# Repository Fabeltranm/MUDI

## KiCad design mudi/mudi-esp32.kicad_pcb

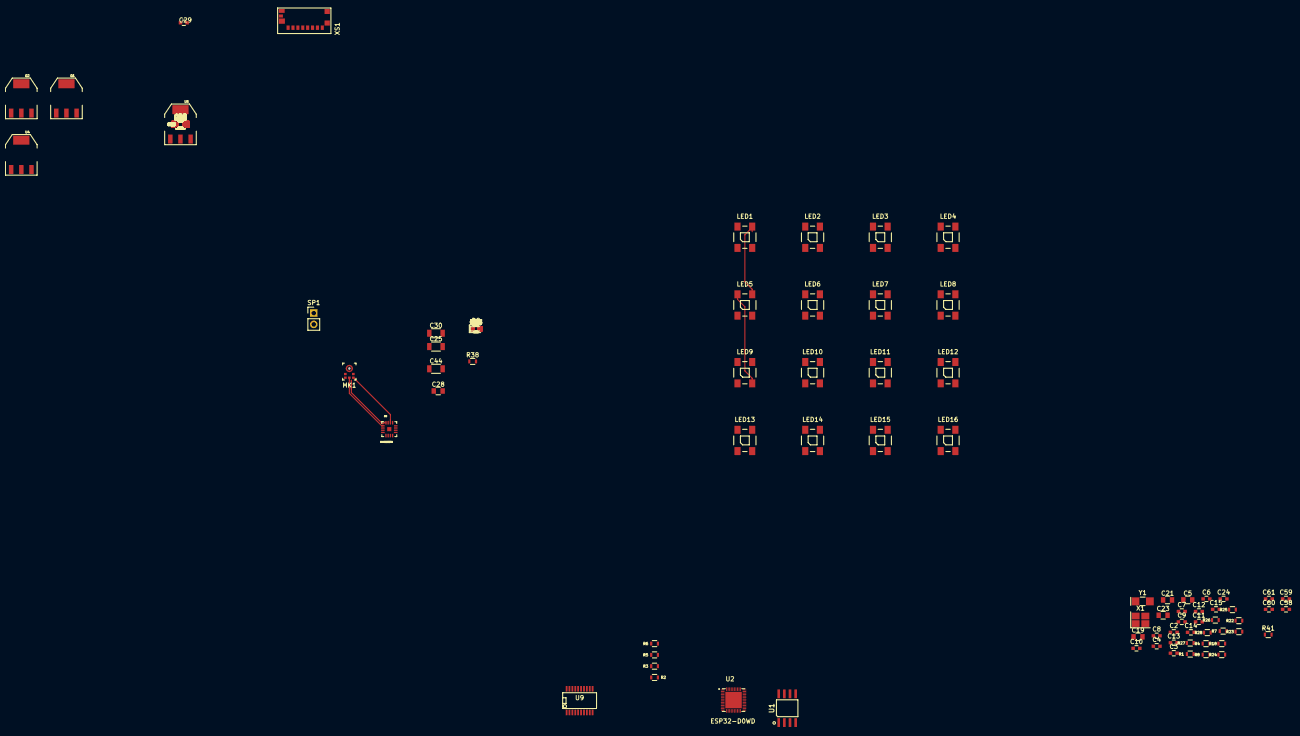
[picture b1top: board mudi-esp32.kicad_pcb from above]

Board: 2 copper layers, 144 parts (0 on the bottom side), 92 nets.

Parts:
C1, C4, C16, C18, C20, C22, C24, C26, C29, C31, C34, C36, C39, C41, C45, C47, C50, C51, C52, C53, C54, C55, C56, C57, C58, C59, C61: 100nF; C_0603
C2, C3: TBD; C_0603
C5, C17, C19, C21, C23: 10uF; C_0805
C6: (NC); C_0603
C7: 100nF (NC); C_0603
C8, C9: 270pF(NC); C_0603
C10: 3.3nF; C_0603
C11, C38, C43: 10nF; C_0603
C12, C13: 10pF; C_0603
C14, C15: 12pF; C_0603
C25, C27, C30, C32, C35, C37, C40, C42: 33uF; C_1206
C28, C33: 4.7uF; C_0805
C44: 10uF; C_1206
C46, C48, C49: 220pF; C_0603
C60: 10nF (16v); C_0603
CF1, CF2, CF6: 100nF; C_0603
CF3: 4.7uf; C_0805
CF4, CF5: 47pF; C_0603
D7: LED; LED_0603
D8: BAT20J; D_SOD-323
F1: PTS08056V050; R_0805
LED1, LED2, LED3, LED4, LED5, LED6, LED7, LED8, LED9, LED10, LED11, LED12, LED13, LED14, LED15, LED16: WS2812B
MK1: SPH0645LM4H-B; SPH0645LM4H
Q1, Q2: PZT2222A; SOT-223
R1, R4, R7, R8: 510R; R_0603
R2, R3, R5, R6, R15, R17, R19, R20, R22, R23, R24, R25, R26, R27, R36, R40: 0R; R_0603
R9, R10, R11, R12, R13, R32: 10k; R_0603
R14: 10k (NC); R_0603
R16, R21: 0R (NC); R_0603
R18: 20k; R_0603
R28: 499R; R_0603
R29, R33: 50R; R_0603
R30, R31, R37, R39: 10K; R_0603
R34: 1K; R_0603
R35: 2K; R_0603
R38: 100K; R_0603
R41: 51R; R_0603
R42, R43: 100k; R_0603
RF1, RF2: 27R; R_0603
SP1: SPEAKER; Pin_Header_Straight_1x02_Pitch2.54mm
U1: W25Q64JV; SOIC-8_208mil
U2: ESP32-D0WD; QFN35P500X500X90-49N
U4, U5: ZLDO1117G33TA; SOT-223
U8: MAX98357A; TQFN16
U9: FT231XS; SSOP-20
X1: ECS-400-10-36-CKY-TR; Crystal_SMD-4pin_2.5x2.0mm
XS1: sdCard; CONN-SD-MICRO-MOLEX_2
Y1: LFXTAL009678; Crystal_SMD_EuroQuartz_EQ161-2pin_3.2x1.5mm_HandSoldering

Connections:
3V3: C4.1, C5.1, C17.1, C18.1, C19.1, C20.1, C21.1, C22.1, C23.1, C24.1, R32.1, U2.1, U2.19, U2.37, U2.43, U2.46
/RGB_LED_Matrix/D1: LED2.4, LED13.2
/RGB_LED_Matrix/D2: LED3.4, LED14.2
/RGB_LED_Matrix/D3: LED4.4, LED15.2
/RGB_LED_Matrix/DIN: LED1.4, R27.1
/RGB_LED_Matrix/Vcc_In(+3.5+5.3): C50.1, C51.1, C52.1, C53.1, C54.1, C55.1, C56.1, C57.1, LED1.1, LED2.1, LED3.1, LED4.1, LED5.1, LED6.1, LED7.1, LED8.1, LED9.1, LED10.1, LED11.1, LED12.1, LED13.1, LED14.1, LED15.1, LED16.1
/audio_voice/BCLK: MK1.4, U8.16
/audio_voice/LRCLK: MK1.1, U8.14
/audio_voice/Vcc_in(3v): C44.1, C45.1, C46.1, C47.1, MK1.5, R42.1, U8.7, U8.8
/esp32/32K_XIN: C14.2, U2.13, Y1.2
/esp32/32K_XP: C15.2, U2.12, Y1.1
/esp32/ENABLE: C16.1, Q2.2, R32.2, U2.9
/esp32/GPIO0: Q1.2, R7.2, R29.1, U2.23
/esp32/GPIO36: C8.1, U2.5
/esp32/GPIO37: C8.2, U2.6
/esp32/GPIO38: C9.1, U2.7
/esp32/GPIO39: C9.2, U2.8
/esp32/JTAG0: R10.2, R19.1, XS1.3
/esp32/JTAG1: R14.2, R16.1, XS1.1
/esp32/JTAG2: R9.2, R17.1, XS1.2
/esp32/JTAG3: R11.2, R15.1, XS1.5
/esp32/SD_D0: R12.2, R20.1, XS1.7
/esp32/SD_D1: R13.2, R21.1, XS1.8
/esp32/TP0: R1.2, R16.2, U2.18
/esp32/TP2: R4.2, R21.2, U2.24
/esp32/TP3: R8.2, U2.16
/esp32/U0DTR: Q1.3, R6.1, R31.1
/esp32/U0RTS: Q2.3, R5.1, R30.2
/esp32/U0RXD: R2.1, U2.40
/esp32/U0TXD: R3.1, R28.2
/esp32/Uart_p0: R2.2, U9.20
/esp32/Uart_p1: R3.2, U9.4
/esp32/Uart_p2: R5.2, U9.2
/esp32/Uart_p3: R6.2, U9.1
/esp32/flash_CS: U1.1, U2.30
/esp32/flash_HOLD: U1.7, U2.28
/esp32/flash_MISO: U1.2, U2.32
/esp32/flash_MOSI: U1.5, U2.33
/esp32/flash_SCK: U1.6, U2.31
/esp32/flash_VDD: C1.1, C7.1, U1.8, U2.26
/esp32/flash_WP: U1.3, U2.29
/imu/Vdd: C58.1, C59.1
/power/3.3v/1A_GND: C31.1, C32.1, U5.2, U5.4
/power/3.3v/1A_GNDD: C29.1, C30.1, U4.2, U4.4
/power/3.3v/150mA_GND: C34.1, C35.1
/power/3.3v/150mA_GNDA: C39.1, C40.1
/power/5v_in: C28.1, CF2.1, CF3.1, D8.2, F1.1, R34.1, R38.1, U9.15
/power/vcc_in: C25.1, D8.1, U4.3
/serial2USB/3.3V_in: CF6.1, U9.3, U9.13, U9.14
/serial2USB/D+: CF5.1, RF2.1
/serial2USB/D-: CF4.2, RF1.1
GND: C1.2, C2.2, C3.2, C4.2, C5.2, C6.2, C7.2, C11.2, C12.2, C13.2, C14.1, C15.1, C16.2, C17.2, C18.2, C19.2, C20.2, C21.2, C22.2, C23.2, C24.2, C26.2, C27.2, C28.2, C31.2, C32.2, C33.2, C34.2, C35.2, C36.2, C37.2, C38.2, C44.2, C45.2, C46.2, C47.2, C48.2, C49.2, C50.2, C51.2, C52.2, C53.2, C54.2, C55.2, C56.2, C57.2, C58.2, C59.2, C60.2, C61.2, CF1.2, CF2.2, CF3.2, CF4.1, CF5.2, CF6.2, LED1.3, LED2.3, LED3.3, LED4.3, LED5.3, LED6.3, LED7.3, LED8.3, LED9.3, LED10.3, LED11.3, LED12.3, LED13.3, LED14.3, LED15.3, LED16.3, MK1.2, MK1.3, R33.1, R35.2, R36.1, R40.1, R43.2, U1.4, U2.49, U5.1, U8.3, U8.11, U8.15, U8.17, U9.6, U9.16, X1.2, X1.4, XS1.6
GNDA: C39.2, C40.2, C41.2, C42.2, C43.2, R40.2
GNDD: C25.2, C29.2, C30.2, R36.2, R38.2, U4.1
unnamed: C2.1, U2.2
unnamed: C6.1, U2.3, U2.4
unnamed: C10.1, C11.1, R18.1, U2.48
unnamed: C10.2, R18.2, U2.47
unnamed: C12.1, U2.44, X1.3
unnamed: C13.1, U2.45, X1.1
unnamed: C26.1, C27.1, U5.3
unnamed: C36.1, C37.1, R37.1
unnamed: C41.1, C42.1, R39.1
unnamed: C48.1, SP1.2, U8.10
unnamed: C49.1, SP1.1, U8.9
unnamed: CF1.1, F1.2
unnamed: D7.2, R34.2
unnamed: LED1.2, LED5.4
unnamed: LED2.2, LED6.4
unnamed: LED3.2, LED7.4
unnamed: LED4.2, LED8.4
unnamed: LED5.2, LED9.4
unnamed: LED6.2, LED10.4
unnamed: LED7.2, LED11.4
unnamed: LED8.2, LED12.4
unnamed: MK1.6, R41.2
unnamed: Q1.1, R30.1
unnamed: Q2.1, R31.2
unnamed: R10.1, R11.1, R12.1, R13.1, R14.1, XS1.4
unnamed: R15.2, U2.17
unnamed: R17.2, U2.20
unnamed: R19.2, U2.21
unnamed: R20.2, U2.22
unnamed: R22.2, U2.34
unnamed: R23.2, U2.35
unnamed: R24.2, U2.36
unnamed: R25.2, U2.38
unnamed: R26.2, U2.39
unnamed: R27.2, U2.42
unnamed: R28.1, U2.41
unnamed: RF1.2, U9.12
unnamed: RF2.2, U9.11

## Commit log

2019-06-13 new pcb
